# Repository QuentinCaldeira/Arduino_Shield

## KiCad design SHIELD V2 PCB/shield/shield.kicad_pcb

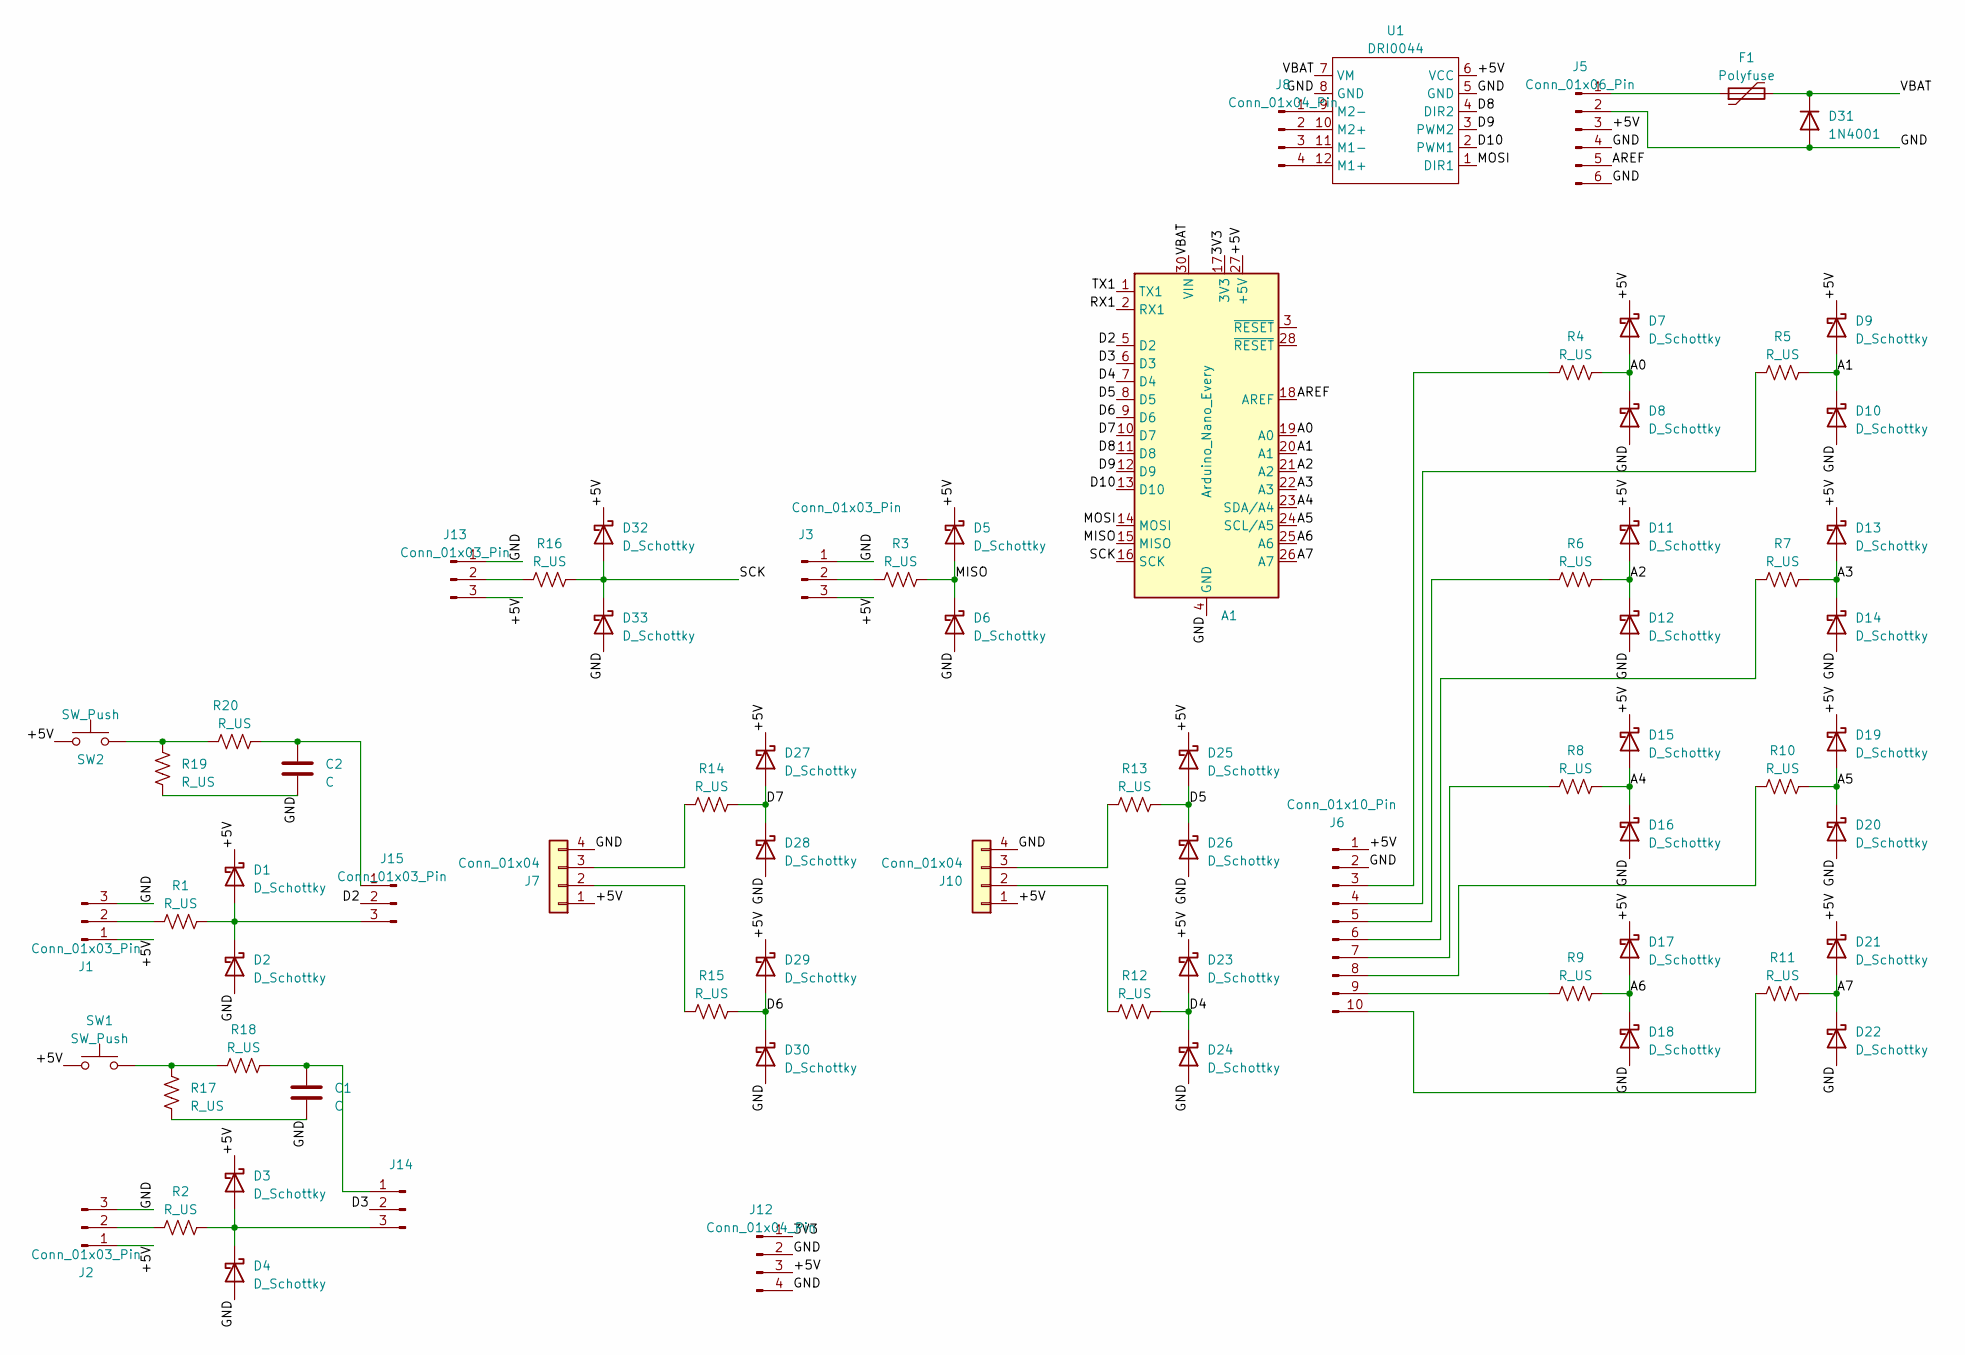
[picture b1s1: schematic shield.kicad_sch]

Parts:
A1: Arduino_Nano_Every; Arduino_Nano_WithMountingHoles
C1, C2: C; capa_10nF
D1, D2, D3, D4, D5, D6, D7, D8, D9, D10, D11, D12, D13, D14, D15, D16, D17, D18, D19, D20, D21, D22, D23, D24, D25, D26, D27, D28, D29, D30, D32, D33: D_Schottky; SOD-123_L2.8-W1.8-LS3.7-RD
D31: 1N4001; D_DO-41_SOD81_P10.16mm_Horizontal
F1: Polyfuse; FUSM4632X85
J1, J2, J3, J13: Conn_01x03_Pin; JST_XH_B3B-XH-AM_1x03_P2.50mm_Vertical
J5: Conn_01x06_Pin; TerminalBlock_Phoenix_MPT-0,5-6-2.54_1x06_P2.54mm_Horizontal
J6: Conn_01x10_Pin; TerminalBlock_Phoenix_MPT-0,5-10-2.54_1x10_P2.54mm_Horizont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
J7, J10: Conn_01x04; JST_XA_B04B-XASK-1_1x04_P2.50mm_Vertical
J8, J12: Conn_01x04_Pin; TerminalBlock_Phoenix_MPT-0,5-4-2.54_1x04_P2.54mm_Horizontal
J14, J15: Conn_01x03_Pin; PinHeader_1x03_P2.54mm_Vertical
R1, R2, R3, R4, R5, R6, R7, R8, R9, R10, R11, R12, R13, R14, R15, R16: R_US; R1210
R17, R18, R19, R20: R_US; R1206
SW1, SW2: SW_Push; SW_TH_Tactile_Omron_B3F-10xx
U1: DRI0044

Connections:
/3V3: A1.17 (3V3), J12.1
/+5V: A1.27 (+5V), D1.1 (K), D3.1 (K), D5.1 (K), D7.1 (K), D9.1 (K), D11.1 (K), D13.1 (K), D15.1 (K), D17.1 (K), D19.1 (K), D21.1 (K), D23.1 (K), D25.1 (K), D27.1 (K), D29.1 (K), D32.1 (K), J1.1, J2.1, J3.3, J5.3, J6.1, J7.1, J10.1, J12.3, J13.3, SW1.1, SW2.1, U1.6 (VCC)
/A0: A1.19 (A0), D7.2 (A), D8.1 (K), R4.2
/A1: A1.20 (A1), D9.2 (A), D10.1 (K), R5.2
/A2: A1.21 (A2), D11.2 (A), D12.1 (K), R6.2
/A3: A1.22 (A3), D13.2 (A), D14.1 (K), R7.2
/A4: A1.23 (SDA/A4), D15.2 (A), D16.1 (K), R8.2
/A5: A1.24 (SCL/A5), D19.2 (A), D20.1 (K), R10.2
/A6: A1.25 (A6), D17.2 (A), D18.1 (K), R9.2
/A7: A1.26 (A7), D21.2 (A), D22.1 (K), R11.2
/AREF: A1.18 (AREF), J5.5
/D2: A1.5 (D2), J15.2
/D3: A1.6 (D3), J14.2
/D4: A1.7 (D4), D23.2 (A), D24.1 (K), R12.2
/D5: A1.8 (D5), D25.2 (A), D26.1 (K), R13.2
/D6: A1.9 (D6), D29.2 (A), D30.1 (K), R15.2
/D7: A1.10 (D7), D27.2 (A), D28.1 (K), R14.2
/D8: A1.11 (D8), U1.4 (DIR2)
/D9: A1.12 (D9), U1.3 (PWM2)
/D10: A1.13 (D10), U1.2 (PWM1)
/GND: A1.4 (GND), A1.29 (GND), C1.2, C2.2, D2.2 (A), D4.2 (A), D6.2 (A), D8.2 (A), D10.2 (A), D12.2 (A), D14.2 (A), D16.2 (A), D18.2 (A), D20.2 (A), D22.2 (A), D24.2 (A), D26.2 (A), D28.2 (A), D30.2 (A), D31.2 (A), D33.2 (A), J1.3, J2.3, J3.1, J5.2, J5.4, J5.6, J6.2, J7.4, J10.4, J12.2, J12.4, J13.1, R17.1, R19.1, U1.5 (GND), U1.8 (GND)
/MISO: A1.15 (MISO), D5.2 (A), D6.1 (K), R3.2
/MOSI: A1.14 (MOSI), U1.1 (DIR1)
/RX1: A1.2 (RX1)
/SCK: A1.16 (SCK), D32.2 (A), D33.1 (K), R16.2
/TX1: A1.1 (TX1)
/VBAT: A1.30 (VIN), D31.1 (K), F1.2, U1.7 (VM)
unnamed: D1.2 (A), D2.1 (K), J15.3, R1.2
unnamed: D3.2 (A), D4.1 (K), J14.3, R2.2
unnamed: J1.2, R1.1
unnamed: J2.2, R2.1
unnamed: J3.2, R3.1
unnamed: F1.1, J5.1
unnamed: J6.3, R4.1
unnamed: J6.4, R5.1
unnamed: J6.5, R6.1
unnamed: J6.6, R7.1
unnamed: J6.7, R8.1
unnamed: J6.8, R10.1
unnamed: J6.9, R9.1
unnamed: J6.10, R11.1
unnamed: J7.2, R15.1
unnamed: J7.3, R14.1
unnamed: J8.1, U1.9 (M2-)
unnamed: J8.2, U1.10 (M2+)
unnamed: J8.3, U1.11 (M1-)
unnamed: J8.4, U1.12 (M1+)
unnamed: J10.2, R12.1
unnamed: J10.3, R13.1
unnamed: J13.2, R16.1
unnamed: C1.1, J14.1, R18.1
unnamed: C2.1, J15.1, R20.1
unnamed: R17.2, R18.2, SW1.2
unnamed: R19.2, R20.2, SW2.2

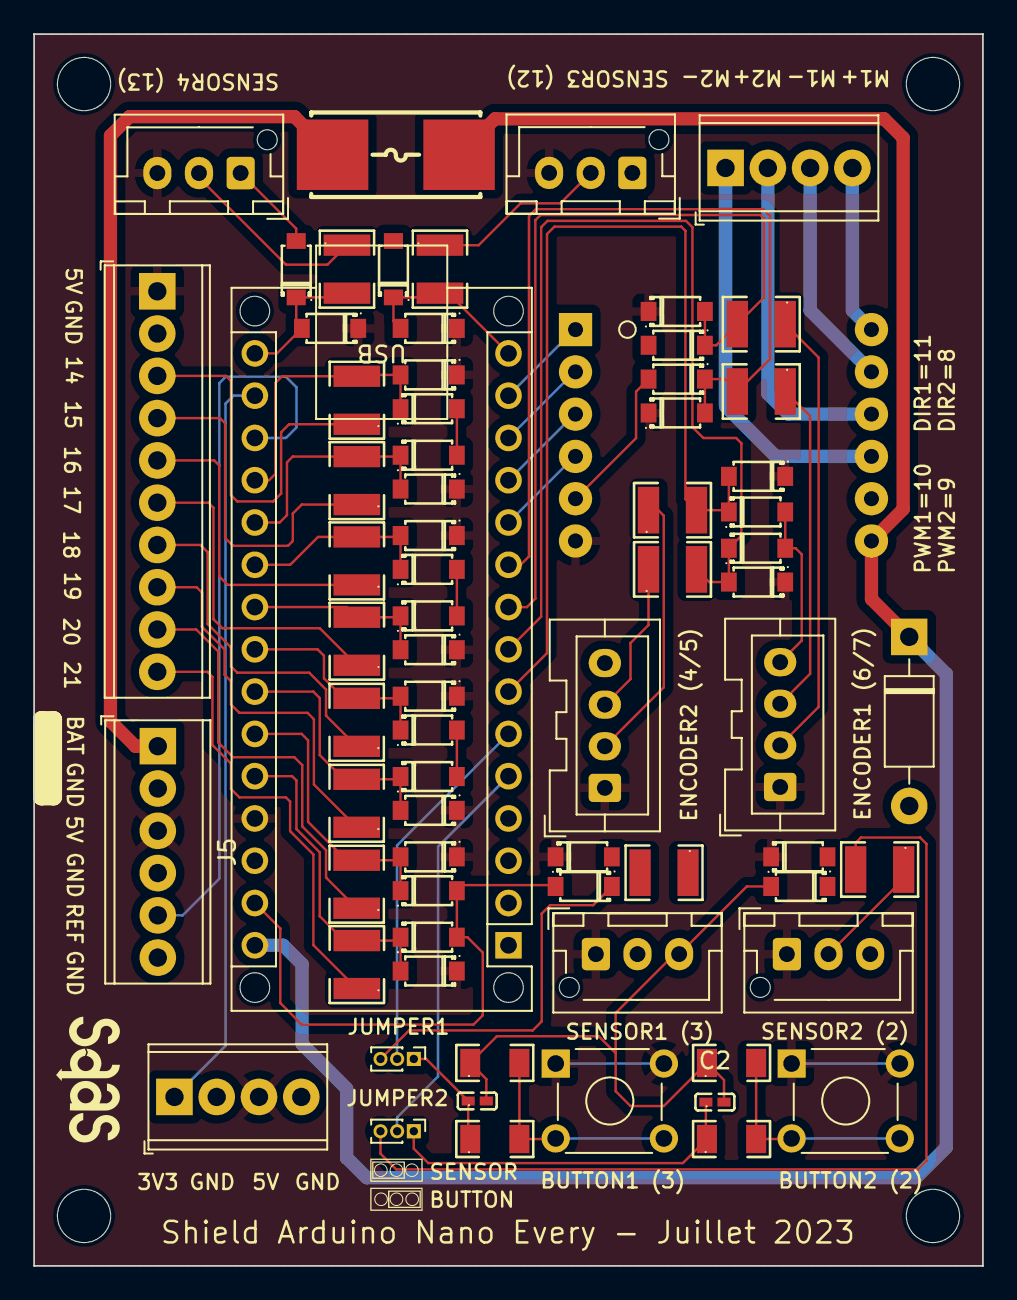
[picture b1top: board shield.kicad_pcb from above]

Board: 2 copper layers, 57.0 x 74.0 mm, 72 parts (0 on the bottom side), 52 nets.

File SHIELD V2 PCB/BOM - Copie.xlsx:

Comment | Designator | Footprint | JLCPCB Part #（optional）
330 | R1, R2, R3, R4, R5, R6, R7, R8, R9, R10, R11, R12, R13, R14, R15, R16 |  | C2933855
10k | R18, R20 |  | C3013377
Diode Schottky | D1, D2, D3, D4, D5, D6, D7, D8, D9, D10, D11, D12, D13, D14, D15, D16, D17, D18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 |  | C8572
Diode | D31 |  | C2456
SMD | F1 |  | C108518
15nF | C1, C2 |  | C363529
110k | R17, R19 |  | C102274
 | J13, J3, J2, J1 |  | C161870
 | J10, J7 |  | C264994
 | J9, J11, J17, J6, J12, J19, J18, J4 |  | C2840316

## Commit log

2023-07-20 Update repo with doc and pcb
2023-08-03 Add a V2 board
    Bigger text and less screw terminals
2023-08-03 Correct document
